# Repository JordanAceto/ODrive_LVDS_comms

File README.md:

# Set of small PCBs for Odrive ◄► motor encoder comms

- One board sits on an Odrive
- The other goes inside a gimbal motor
- They are connected with twisted pair wire
- The goal is to increase noise immunity and have convenient connectors
- One Odrive board can connect to two encoder boards

---

### Connectors used
- JST GH series 9 pin

---

### IMPORTANT NOTE 1
- The encoder board PCB should be 1mm thick
- The ODRive board can be any thickness you like

---

### IMPORTANT NOTE 2
- The two SN65LVDS050PW chips on the ODrive board will conflict if you use only one motor at a time
- Setting the chip select line high for a given SN65LVDS050PW chip puts its SDI pin into a high impedance state
- If the chip select line is low or not active, the SN65LVDS050PW chip will assert its output on the shared SDI line
- When using only 1 motor there are two options:
  - set the chip select line for the unused SN65LVDS050PW permanently high
  - only solder one SN65LVDS050PW chip

---

### Status
- test build done, safe to order boards

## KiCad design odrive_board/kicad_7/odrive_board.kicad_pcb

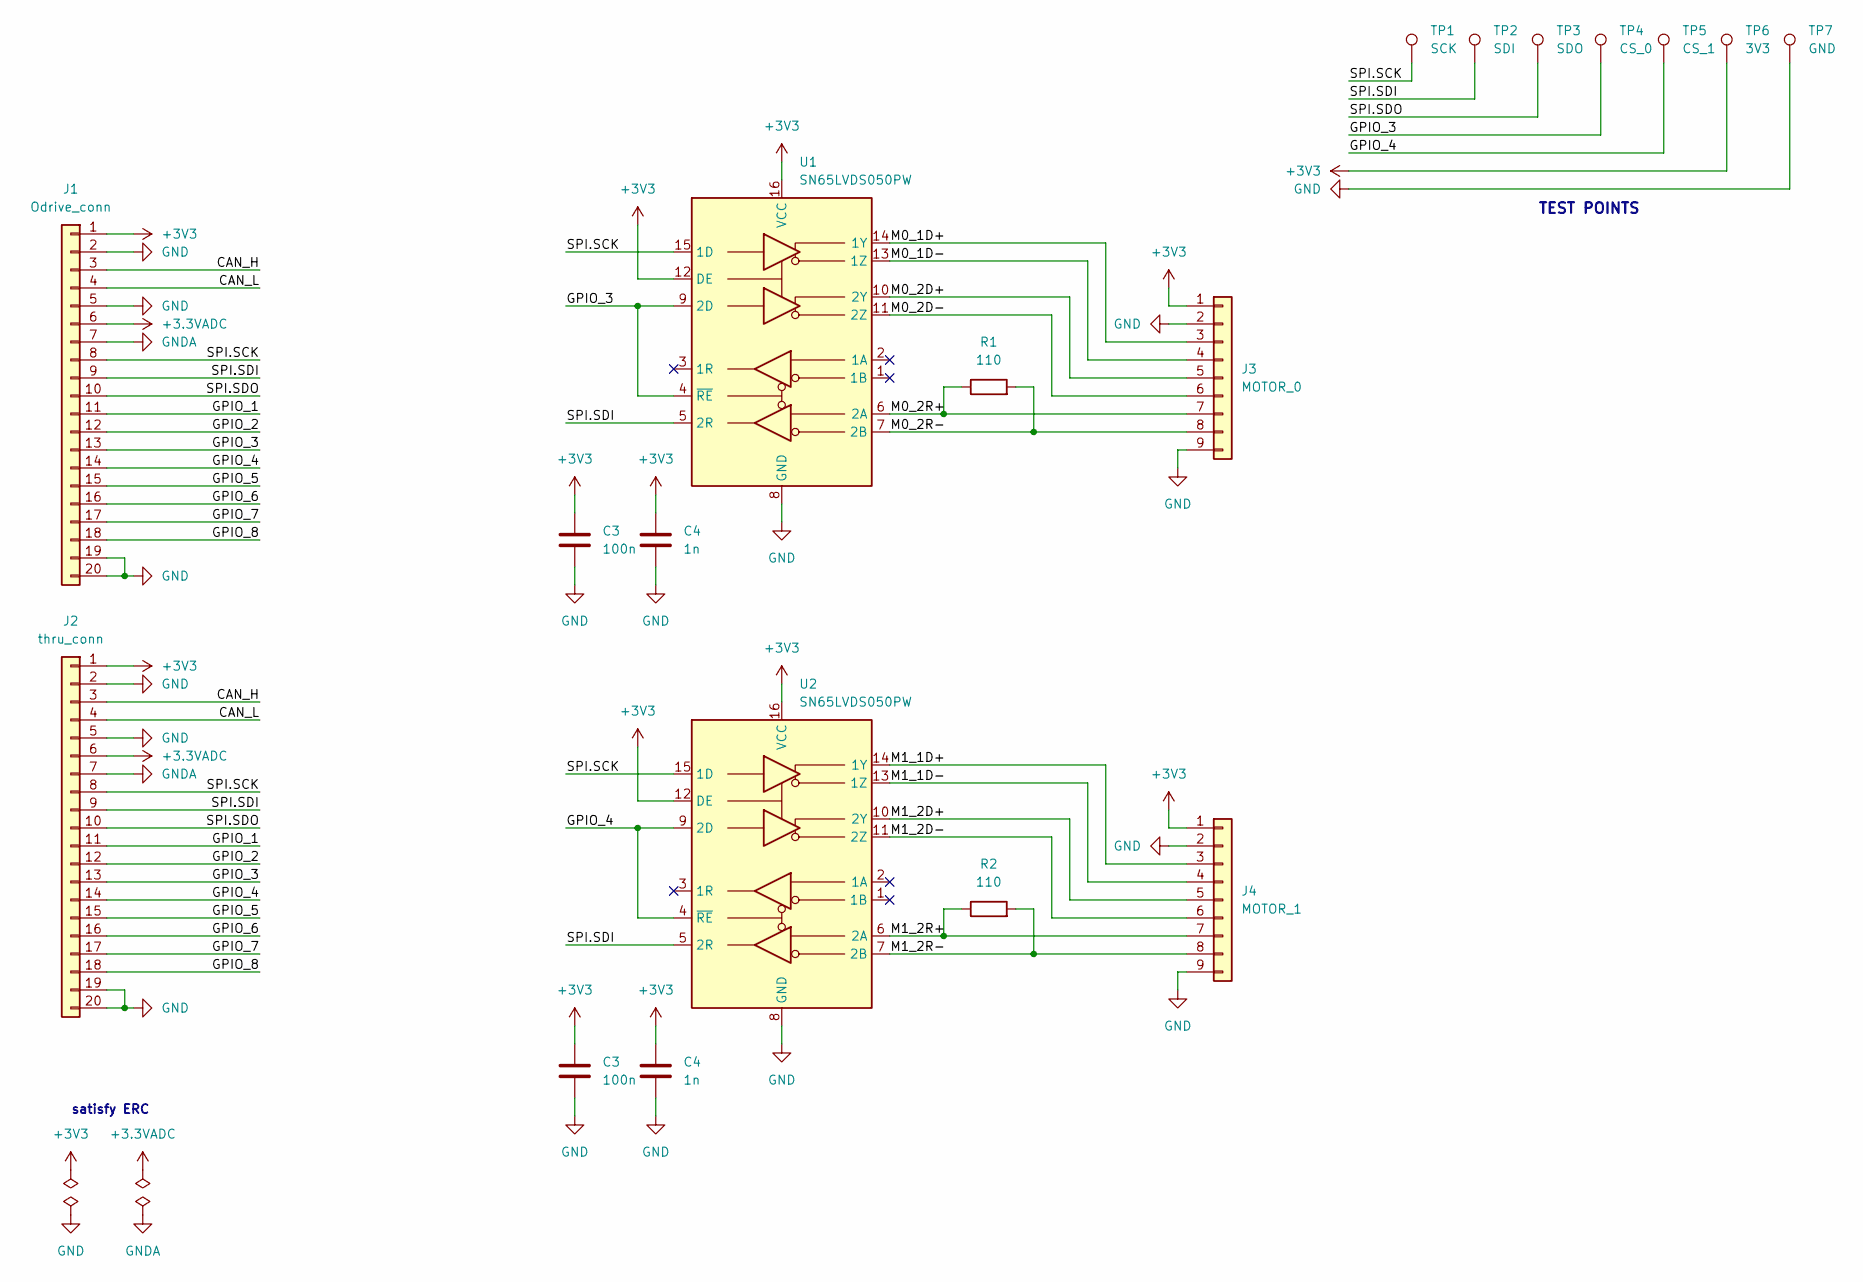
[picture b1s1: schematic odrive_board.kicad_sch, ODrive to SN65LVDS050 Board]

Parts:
C3: 100n; C_0603_1608Metric
C4: 1n; C_0603_1608Metric
J1: Odrive_conn; PinHeader_1x20_P2.54mm_Vertical
J2: thru_conn; PinHeader_1x20_P2.54mm_Vertical
J3: MOTOR_0; JST_GH_SM09B-GHS-TB_1x09-1MP_P1.25mm_Horizontal
J4: MOTOR_1; JST_GH_SM09B-GHS-TB_1x09-1MP_P1.25mm_Horizontal
R1, R2: 110; R_0603_1608Metric
TP1: SCK; TestPoint_Keystone_5000-5004_Miniature
TP2: SDI; TestPoint_Keystone_5000-5004_Miniature
TP3: SDO; TestPoint_Keystone_5000-5004_Miniature
TP4: CS_0; TestPoint_Keystone_5000-5004_Miniature
TP5: CS_1; TestPoint_Keystone_5000-5004_Miniature
TP6: 3V3; TestPoint_Keystone_5000-5004_Miniature
TP7: GND; TestPoint_Bridge_Pitch5.08mm_Drill0.7mm
U1, U2: SN65LVDS050PW; TSSOP-16_4.4x5mm_P0.65mm

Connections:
+3.3VADC: J1.6, J2.6
+3V3: C3.1, C4.1, J1.1, J2.1, J3.1, J4.1, TP6.1, U1.12 (DE), U1.16 (VCC), U2.12 (DE), U2.16 (VCC); also elsewhere on the board
/CAN_H: J1.3, J2.3
/CAN_L: J1.4, J2.4
/GPIO_1: J1.11, J2.11
/GPIO_2: J1.12, J2.12
/GPIO_3: J1.13, J2.13, TP4.1, U1.4 (~RE), U1.9 (2D)
/GPIO_4: J1.14, J2.14, TP5.1, U2.4 (~RE), U2.9 (2D)
/GPIO_5: J1.15, J2.15
/GPIO_6: J1.16, J2.16
/GPIO_7: J1.17, J2.17
/GPIO_8: J1.18, J2.18
/M0_1D+: J3.3, U1.14 (1Y)
/M0_1D-: J3.4, U1.13 (1Z)
/M0_2D+: J3.5, U1.10 (2Y)
/M0_2D-: J3.6, U1.11 (2Z)
/M0_2R+: J3.7, R1.1, U1.6 (2A)
/M0_2R-: J3.8, R1.2, U1.7 (2B)
/M1_1D+: J4.3, U2.14 (1Y)
/M1_1D-: J4.4, U2.13 (1Z)
/M1_2D+: J4.5, U2.10 (2Y)
/M1_2D-: J4.6, U2.11 (2Z)
/M1_2R+: J4.7, R2.1, U2.6 (2A)
/M1_2R-: J4.8, R2.2, U2.7 (2B)
/SPI.SCK: J1.8, J2.8, TP1.1, U1.15 (1D), U2.15 (1D)
/SPI.SDI: J1.9, J2.9, TP2.1, U1.5 (2R), U2.5 (2R)
/SPI.SDO: J1.10, J2.10, TP3.1
GND: C3.2, C4.2, J1.2, J1.5, J1.19, J1.20, J2.2, J2.5, J2.19, J2.20, J3.2, J3.9, J4.2, J4.9, TP7.1, U1.8 (GND), U2.8 (GND); also elsewhere on the board
GNDA: J1.7, J2.7

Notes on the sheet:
satisfy ERC
TEST POINTS

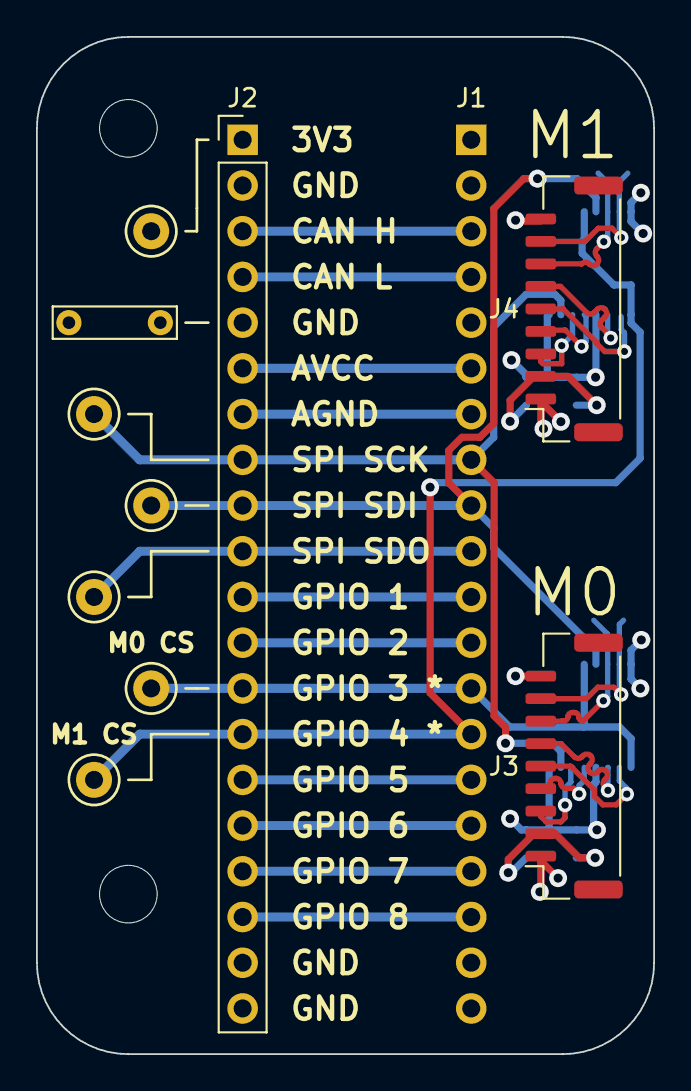
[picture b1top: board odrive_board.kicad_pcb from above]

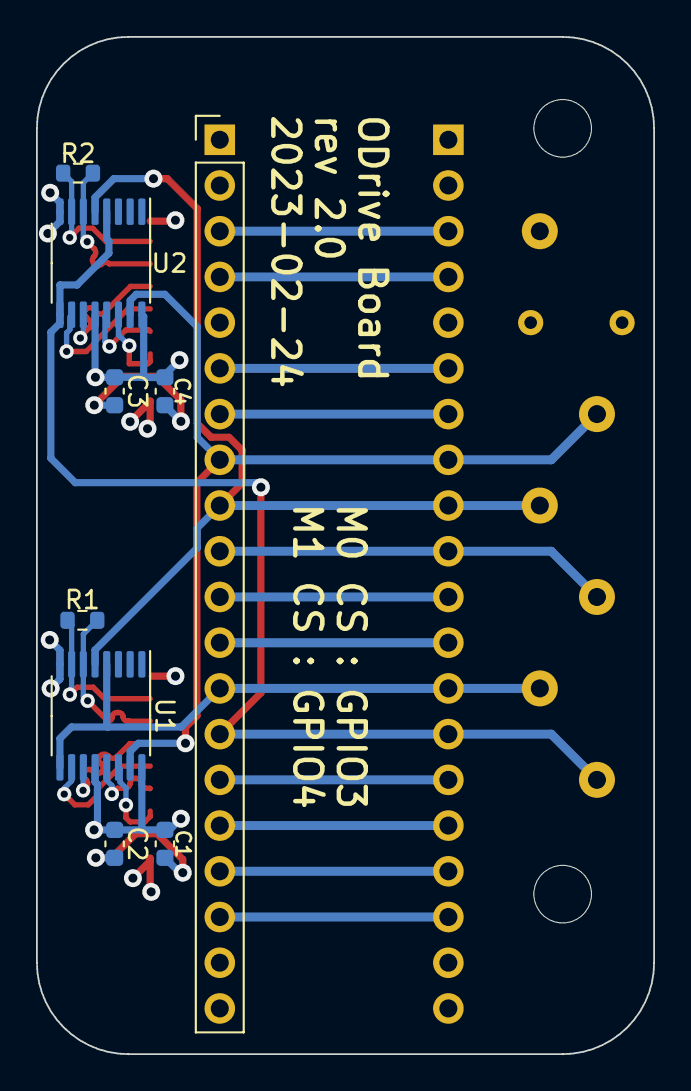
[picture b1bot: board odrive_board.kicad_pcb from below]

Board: 4 copper layers, 34.3 x 56.5 mm, 19 parts (9 on the bottom side), 29 nets.

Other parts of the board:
C1: 100n; C_0603_1608Metric
C2: 1n; C_0603_1608Metric

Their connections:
+3V3: C1.1, C2.1; also elsewhere on the board
GND: C1.2, C2.2; also elsewhere on the board

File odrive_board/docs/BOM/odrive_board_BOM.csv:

"#","Reference","Qty","Value","Footprint","DNP"
"1","C1, C3","2","100n","Capacitor_SMD:C_0603_1608Metric",""
"2","C2, C4","2","1n","Capacitor_SMD:C_0603_1608Metric",""
"3","J1","1","Odrive_conn","Connector_PinHeader_2.54mm:PinHeader_1x20_P2.54mm_Vertical",""
"4","J2","1","thru_conn","Connector_PinHeader_2.54mm:PinHeader_1x20_P2.54mm_Vertical",""
"5","J3","1","MOTOR_0","Connector_JST:JST_GH_SM09B-GHS-TB_1x09-1MP_P1.25mm_Horizontal",""
"6","J4","1","MOTOR_1","Connector_JST:JST_GH_SM09B-GHS-TB_1x09-1MP_P1.25mm_Horizontal",""
"7","R1, R2","2","110","Resistor_SMD:R_0603_1608Metric",""
"8","TP1","1","SCK","TestPoint:TestPoint_Keystone_5000-5004_Miniature",""
"9","TP2","1","SDI","TestPoint:TestPoint_Keystone_5000-5004_Miniature",""
"10","TP3","1","SDO","TestPoint:TestPoint_Keystone_5000-5004_Miniature",""
"11","TP4","1","CS_0","TestPoint:TestPoint_Keystone_5000-5004_Miniature",""
"12","TP5","1","CS_1","TestPoint:TestPoint_Keystone_5000-5004_Miniature",""
"13","TP6","1","3V3","TestPoint:TestPoint_Keystone_5000-5004_Miniature",""
"14","TP7","1","GND","TestPoint:TestPoint_Bridge_Pitch5.08mm_Drill0.7mm",""
"15","U1, U2","2","SN65LVDS050PW","Package_SO:TSSOP-16_4.4x5mm_P0.65mm",""

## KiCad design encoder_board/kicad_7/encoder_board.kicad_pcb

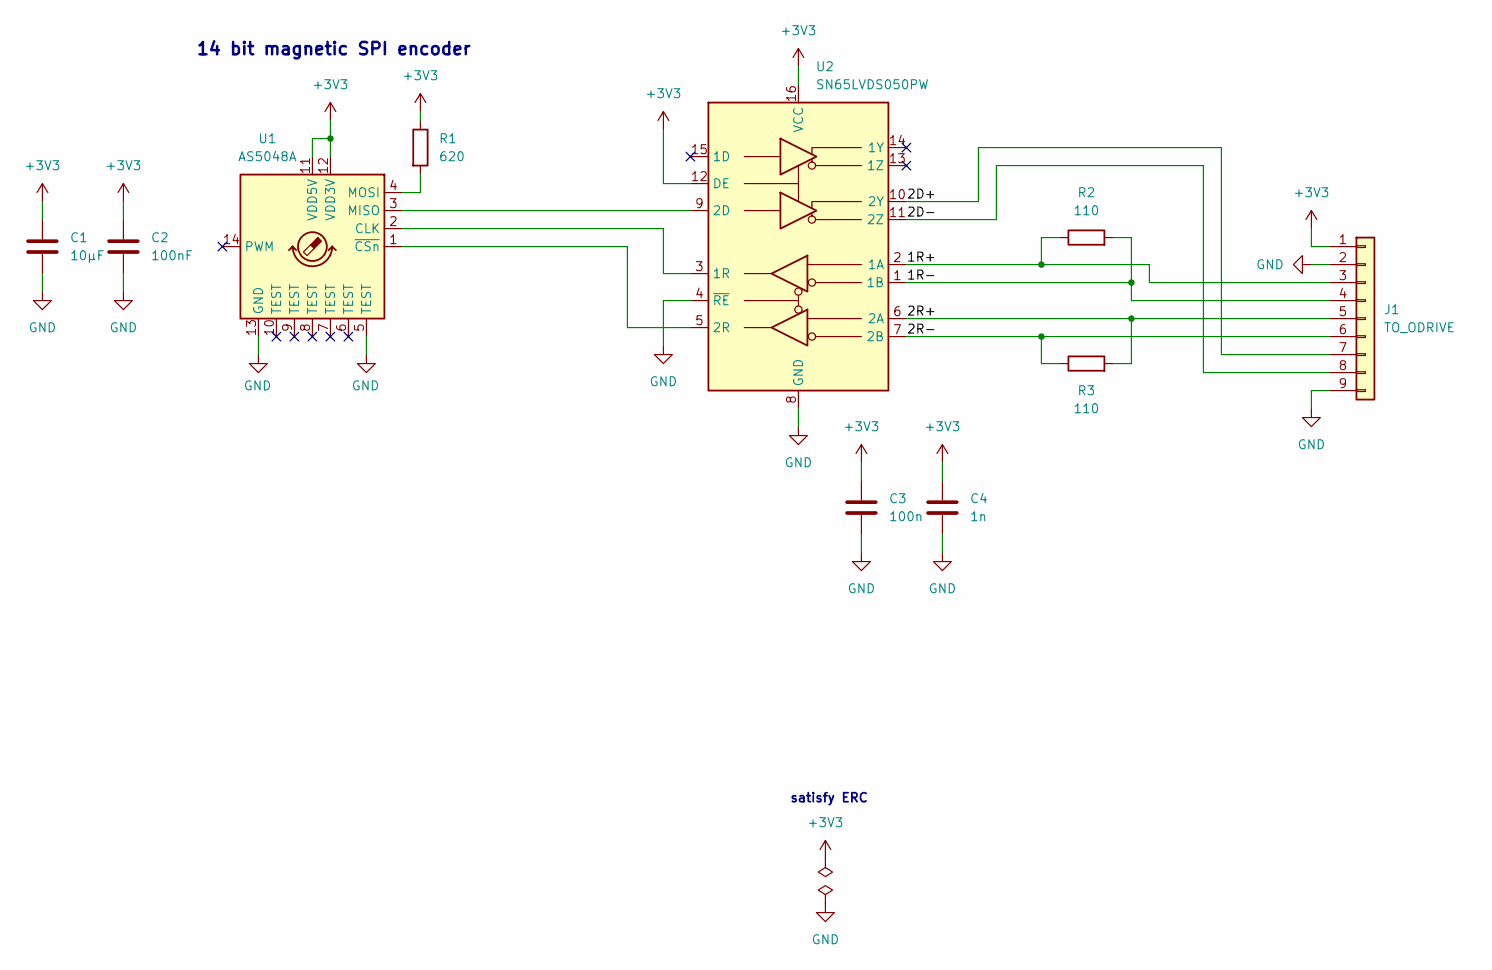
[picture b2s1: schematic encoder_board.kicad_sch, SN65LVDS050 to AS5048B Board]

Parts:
C1: 10µF; C_0603_1608Metric
C2: 100nF; C_0603_1608Metric
C3: 100n; C_0603_1608Metric
C4: 1n; C_0603_1608Metric
J1: TO_ODRIVE; JST_GH_SM09B-GHS-TB_1x09-1MP_P1.25mm_Horizontal
R1: 620; R_0603_1608Metric
R2, R3: 110; R_0603_1608Metric
U1: AS5048A; TSSOP-14_4.4x5mm_P0.65mm; Part AS5048A
U2: SN65LVDS050PW; TSSOP-16_4.4x5mm_P0.65mm

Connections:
+3V3: C1.1, C2.1, C3.1, C4.1, J1.1, R1.1, U1.11 (VDD5V), U1.12 (VDD3V), U2.12 (DE), U2.16 (VCC)
/1R+: J1.3, R2.1, U2.2 (1A)
/1R-: J1.4, R2.2, U2.1 (1B)
/2D+: J1.7, U2.10 (2Y)
/2D-: J1.8, U2.11 (2Z)
/2R+: J1.5, R3.2, U2.6 (2A)
/2R-: J1.6, R3.1, U2.7 (2B)
GND: C1.2, C2.2, C3.2, C4.2, J1.2, J1.9, U1.5 (TEST), U1.13 (GND), U2.4 (~RE), U2.8 (GND)
unnamed: U1.2 (CLK), U2.3 (1R)
unnamed: U1.3 (MISO), U2.9 (2D)
unnamed: R1.2, U1.4 (MOSI)
unnamed: U1.1 (~CSn), U2.5 (2R)

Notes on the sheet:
14 bit magnetic SPI encoder
satisfy ERC

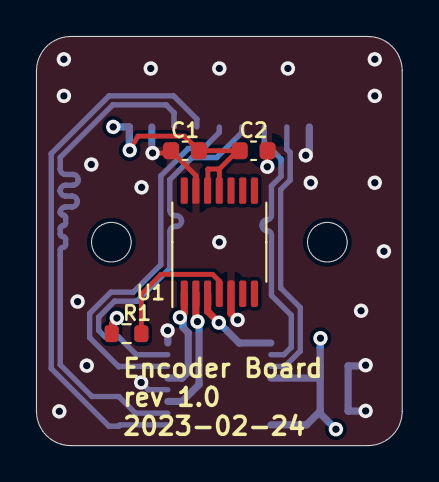
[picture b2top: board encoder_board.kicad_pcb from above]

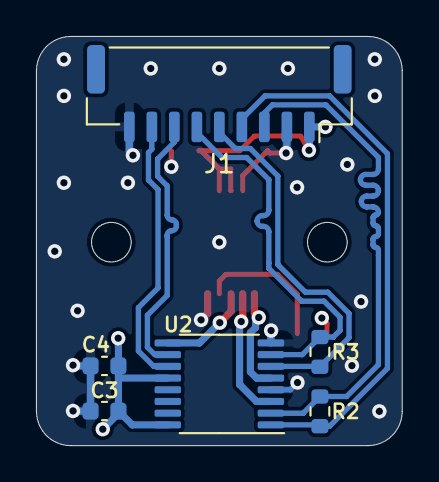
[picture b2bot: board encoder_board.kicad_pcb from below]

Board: 4 copper layers, 20.3 x 22.7 mm, 12 parts (6 on the bottom side), 12 nets.

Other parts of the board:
H1, H2: MountingHole; MountingHole_2.2mm_M2

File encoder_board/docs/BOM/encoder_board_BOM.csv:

"#","Reference","Qty","Value","Footprint","DNP"
"1","C1","1","10µF","Capacitor_SMD:C_0603_1608Metric",""
"2","C2","1","100nF","Capacitor_SMD:C_0603_1608Metric",""
"3","C3","1","100n","Capacitor_SMD:C_0603_1608Metric",""
"4","C4","1","1n","Capacitor_SMD:C_0603_1608Metric",""
"5","J1","1","TO_ODRIVE","Connector_JST:JST_GH_SM09B-GHS-TB_1x09-1MP_P1.25mm_Horizontal",""
"6","R1","1","620","Resistor_SMD:R_0603_1608Metric",""
"7","R2, R3","2","110","Resistor_SMD:R_0603_1608Metric",""
"8","U1","1","AS5048A","Package_SO:TSSOP-14_4.4x5mm_P0.65mm",""
"9","U2","1","SN65LVDS050PW","Package_SO:TSSOP-16_4.4x5mm_P0.65mm",""

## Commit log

2023-02-27 Add licence
2023-02-27 Add note about encoder thickness
2023-02-27 Add missing drill files to compressed gerbers
2023-03-22 Update readme after successful test build

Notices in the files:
encoder_board/kicad_7/encoder_board.kicad_pcb:
creativecommons.org/licences/by/4.0
Licence: CC by 4.0
encoder_board/kicad_7/encoder_board.kicad_sch:
License: CC by 4.0
